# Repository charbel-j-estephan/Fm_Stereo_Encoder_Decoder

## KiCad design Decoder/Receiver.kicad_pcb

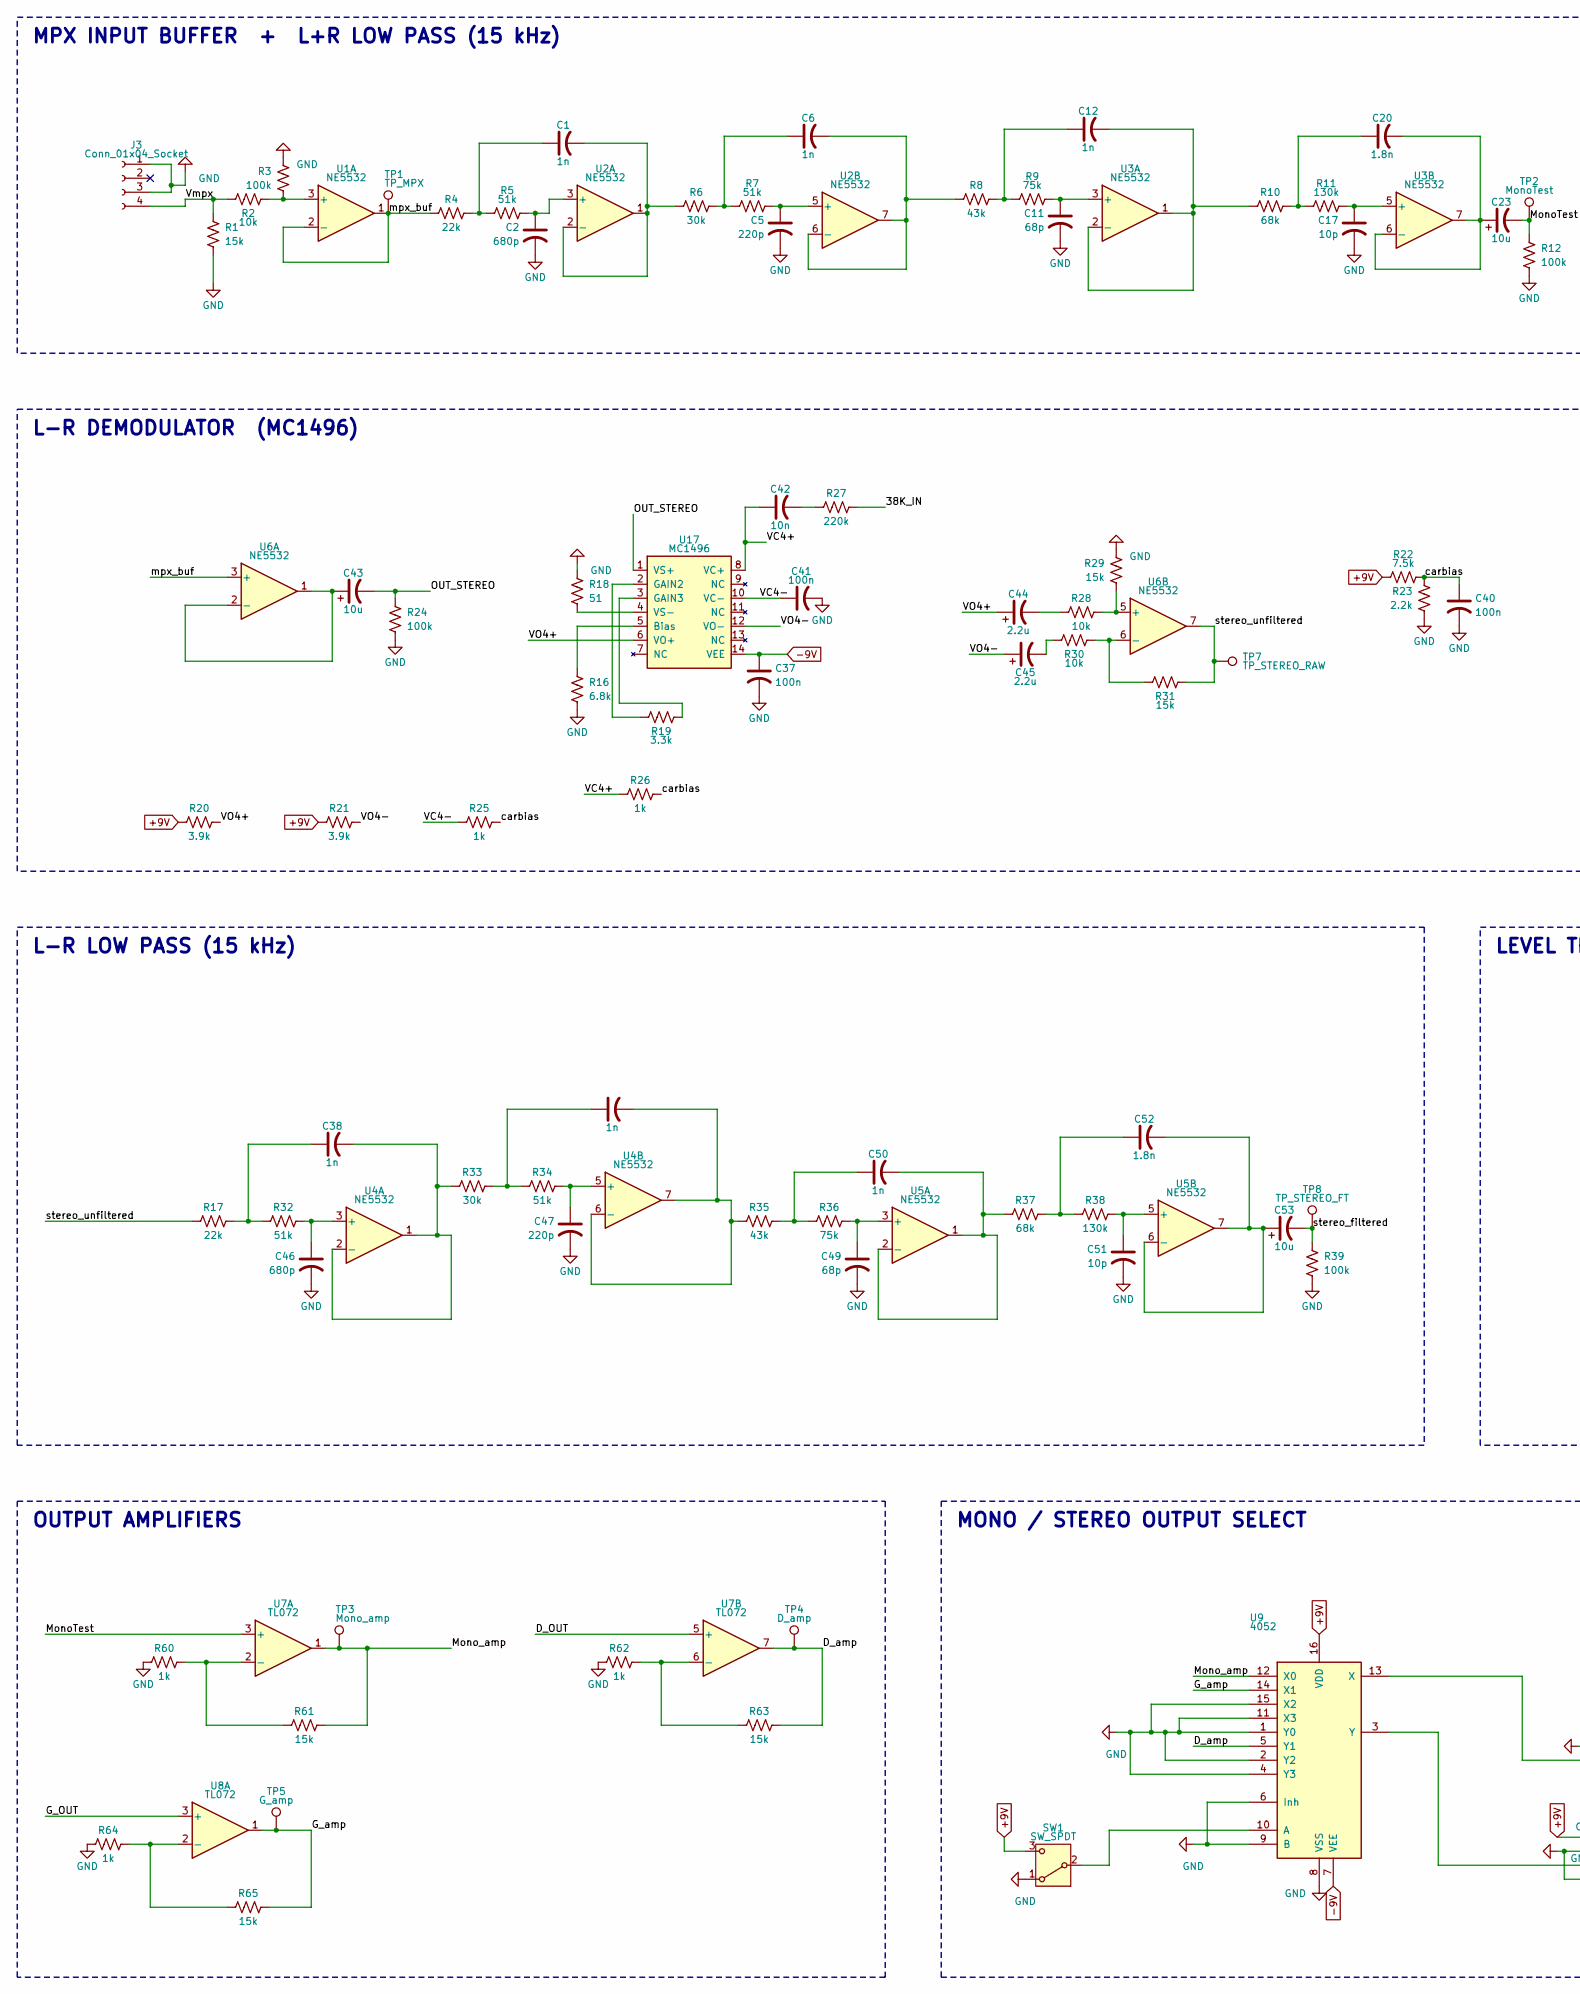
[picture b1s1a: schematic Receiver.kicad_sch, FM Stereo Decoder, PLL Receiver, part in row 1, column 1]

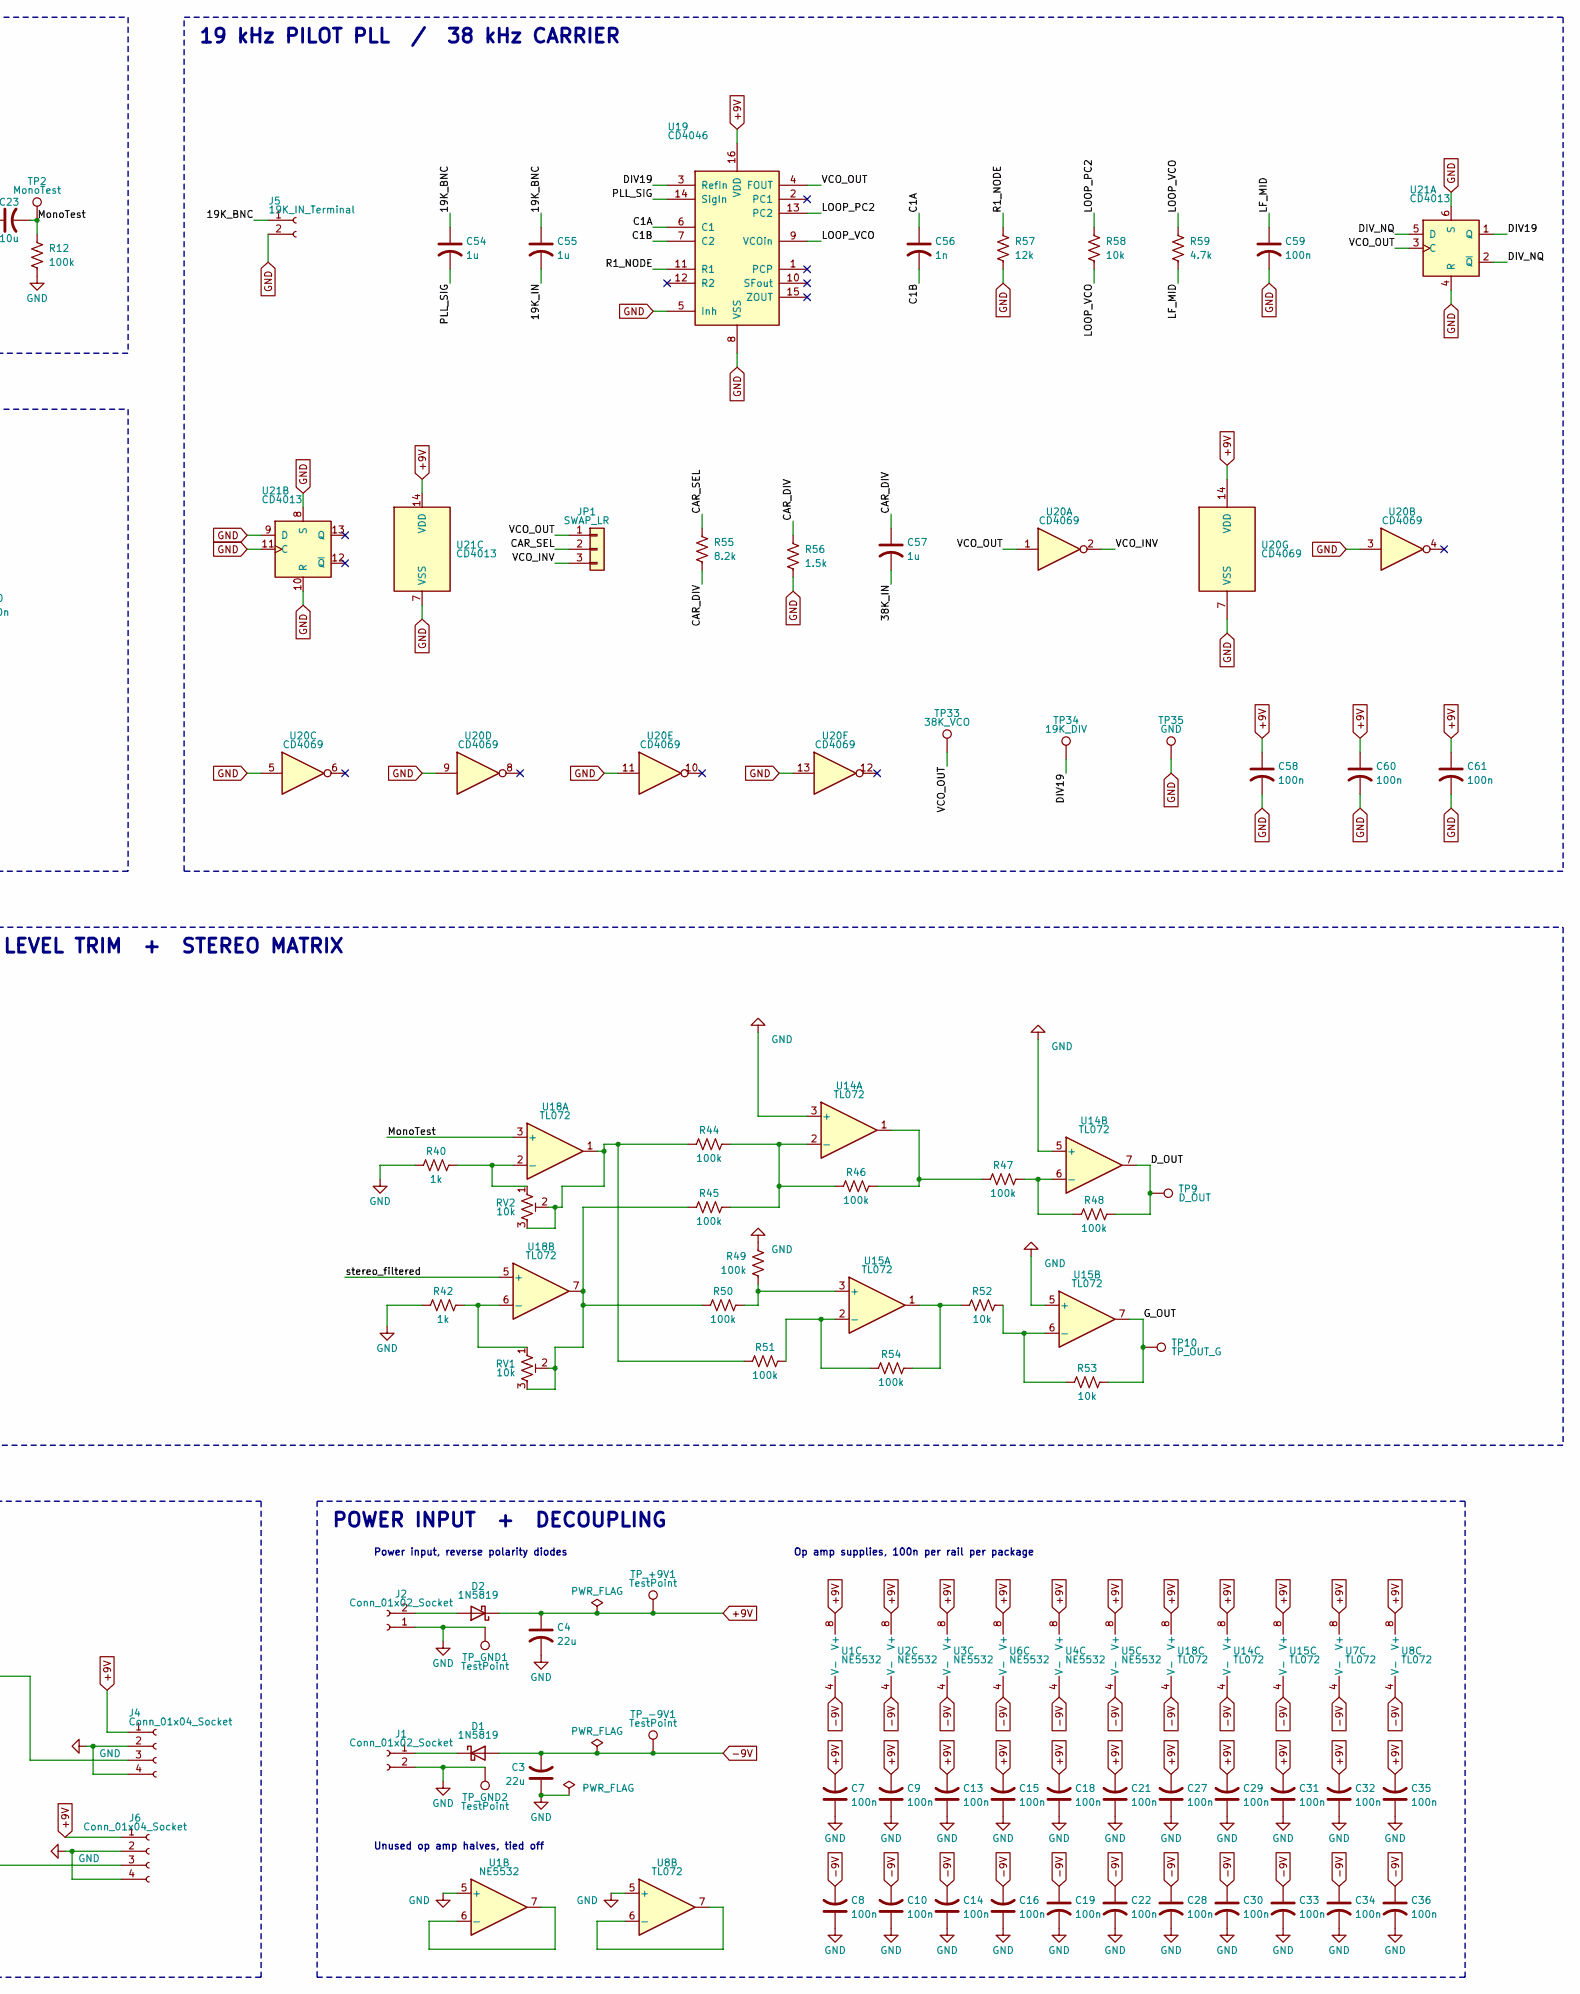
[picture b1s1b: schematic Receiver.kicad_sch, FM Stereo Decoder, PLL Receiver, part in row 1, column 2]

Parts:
C1, C6, C12, C38, C48, C50, C56: 1n; C_Disc_D5.0mm_W2.5mm_P5.00mm
C2, C46: 680p; C_Disc_D5.0mm_W2.5mm_P5.00mm
C3, C4: 22u; CP_Radial_D8.0mm_P3.50mm
C5, C47: 220p; C_Disc_D5.0mm_W2.5mm_P5.00mm
C7, C8, C9, C10, C13, C14, C15, C16, C18, C19, C21, C22, C27, C28, C29, C30, C31, C32, C33, C34, C35, C36, C37, C40, C41, C58, C59, C60, C61: 100n; C_Disc_D5.0mm_W2.5mm_P5.00mm
C11, C49: 68p; C_Disc_D5.0mm_W2.5mm_P5.00mm
C17, C51: 10p; C_Disc_D5.0mm_W2.5mm_P5.00mm
C20, C52: 1.8n; C_Disc_D5.0mm_W2.5mm_P5.00mm
C23, C43, C53: 10u; CP_Radial_D6.3mm_P2.50mm
C42: 10n; C_Disc_D5.0mm_W2.5mm_P5.00mm
C44, C45: 2.2u; CP_Radial_D6.3mm_P2.50mm
C54, C55, C57: 1u; C_Rect_L7.2mm_W3.5mm_P5.00mm
D1, D2: 1N5819; D_DO-41_SOD81_P10.16mm_Horizontal
J1, J2: Conn_01x02_Socket; TerminalBlock_Phoenix_MKDS-1,5-2-5.08_1x02_P5.08mm_Horizont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
J3: Conn_01x04_Socket; PinHeader_1x04_P2.54mm_Vertical
J4, J6: Conn_01x04_Socket; PinSocket_1x04_P2.54mm_Vertical
J5: 19K_IN_Terminal; TerminalBlock_Phoenix_MKDS-1,5-2-5.08_1x02_P5.08mm_Horizont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
JP1: SWAP_LR; PinHeader_1x03_P2.54mm_Vertical
R1, R29, R31, R61, R63, R65: 15k; R_Axial_DIN0207_L6.3mm_D2.5mm_P10.16mm_Horizontal
R2, R28, R30, R52, R53, R58: 10k; R_Axial_DIN0207_L6.3mm_D2.5mm_P10.16mm_Horizontal
R3, R12, R24, R39, R44, R45, R46, R47, R48, R49, R50, R51, R54: 100k; R_Axial_DIN0207_L6.3mm_D2.5mm_P10.16mm_Horizontal
R4, R17: 22k; R_Axial_DIN0207_L6.3mm_D2.5mm_P10.16mm_Horizontal
R5, R7, R32, R34: 51k; R_Axial_DIN0207_L6.3mm_D2.5mm_P10.16mm_Horizontal
R6, R33: 30k; R_Axial_DIN0207_L6.3mm_D2.5mm_P10.16mm_Horizontal
R8, R35: 43k; R_Axial_DIN0207_L6.3mm_D2.5mm_P10.16mm_Horizontal
R9, R36: 75k; R_Axial_DIN0207_L6.3mm_D2.5mm_P10.16mm_Horizontal
R10, R37: 68k; R_Axial_DIN0207_L6.3mm_D2.5mm_P10.16mm_Horizontal
R11, R38: 130k; R_Axial_DIN0207_L6.3mm_D2.5mm_P10.16mm_Horizontal
R16: 6.8k; R_Axial_DIN0207_L6.3mm_D2.5mm_P10.16mm_Horizontal
R18: 51; R_Axial_DIN0207_L6.3mm_D2.5mm_P10.16mm_Horizontal
R19: 3.3k; R_Axial_DIN0207_L6.3mm_D2.5mm_P10.16mm_Horizontal
R20, R21: 3.9k; R_Axial_DIN0207_L6.3mm_D2.5mm_P10.16mm_Horizontal
R22: 7.5k; R_Axial_DIN0207_L6.3mm_D2.5mm_P10.16mm_Horizontal
R23: 2.2k; R_Axial_DIN0207_L6.3mm_D2.5mm_P10.16mm_Horizontal
R25, R26, R40, R42, R60, R62, R64: 1k; R_Axial_DIN0207_L6.3mm_D2.5mm_P10.16mm_Horizontal
R27: 220k; R_Axial_DIN0207_L6.3mm_D2.5mm_P10.16mm_Horizontal
R55: 8.2k; R_Axial_DIN0207_L6.3mm_D2.5mm_P10.16mm_Horizontal
R56: 1.5k; R_Axial_DIN0207_L6.3mm_D2.5mm_P10.16mm_Horizontal
R57: 12k; R_Axial_DIN0207_L6.3mm_D2.5mm_P10.16mm_Horizontal
R59: 4.7k; R_Axial_DIN0207_L6.3mm_D2.5mm_P10.16mm_Horizontal
RV1, RV2: 10k; Potentiometer_Bourns_3296W_Vertical
SW1: SW_SPDT; PinHeader_1x03_P2.54mm_Vertical
TP1: TP_MPX; PinHeader_1x01_P2.54mm_Vertical
TP2: MonoTest; PinHeader_1x01_P2.54mm_Vertical
TP3: Mono_amp; PinHeader_1x01_P2.54mm_Vertical
TP4: D_amp; PinHeader_1x01_P2.54mm_Vertical
TP5: G_amp; PinHeader_1x01_P2.54mm_Vertical
TP7: TP_STEREO_RAW; PinHeader_1x01_P2.54mm_Vertical
TP8: TP_STEREO_FT; PinHeader_1x01_P2.54mm_Vertical
TP9: D_OUT; PinHeader_1x01_P2.54mm_Vertical
TP10: TP_OUT_G; PinHeader_1x01_P2.54mm_Vertical
TP33: 38K_VCO; PinHeader_1x01_P2.54mm_Vertical
TP34: 19K_DIV; PinHeader_1x01_P2.54mm_Vertical
TP35: GND; PinHeader_1x01_P2.54mm_Vertical
TP_+9V1: TestPoint; PinHeader_1x01_P2.54mm_Vertical
TP_-9V1: TestPoint; PinHeader_1x01_P2.54mm_Vertical
TP_GND1, TP_GND2: TestPoint; PinHeader_1x01_P2.54mm_Vertical
U1, U2, U3, U4, U5, U6: NE5532; DIP-8_W7.62mm_Socket
U7, U8, U14, U15, U18: TL072; DIP-8_W7.62mm_Socket
U9: 4052; DIP-16_W7.62mm_Socket
U17: MC1496; DIP-14_W7.62mm_Socket
U19: CD4046; DIP-16_W7.62mm_Socket
U20: CD4069; DIP-14_W7.62mm_Socket
U21: CD4013; DIP-14_W7.62mm_Socket

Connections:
+9V: C4.1, C7.2, C9.2, C13.2, C15.2, C18.2, C21.2, C27.2, C29.2, C31.2, C32.2, C35.2, C58.1, C60.1, C61.1, D2.1 (K), J4.1, J6.1, R20.2, R21.2, R22.2, SW1.3 (C), TP_+9V1.1 (1_1), U1.8 (V+), U2.8 (V+), U3.8 (V+), U4.8 (V+), U5.8 (V+), U6.8 (V+), U7.8 (V+), U8.8 (V+), U9.16 (VDD), U14.8 (V+), U15.8 (V+), U18.8 (V+), U19.16 (VDD), U20.14 (VDD), U21.14 (VDD)
-9V: C3.2, C8.2, C10.2, C14.2, C16.2, C19.1, C22.1, C28.1, C30.1, C33.1, C34.1, C36.1, C37.1, D1.2 (A), TP_-9V1.1 (1_1), U1.4 (V-), U2.4 (V-), U3.4 (V-), U4.4 (V-), U5.4 (V-), U6.4 (V-), U7.4 (V-), U8.4 (V-), U9.7 (VEE), U14.4 (V-), U15.4 (V-), U17.14 (VEE), U18.4 (V-)
/19K_BNC: C54.1, C55.1, J5.1
/19K_IN: C55.2
/38K_IN: C57.2, R27.1
/C1A: C56.1, U19.6 (C1)
/C1B: C56.2, U19.7 (C2)
/CAR_DIV: C57.1, R55.2, R56.1
/CAR_SEL: JP1.2, R55.1
/DIV19: TP34.1 (1_1), U19.3 (RefIn), U21.1 (Q)
/DIV_NQ: U21.2 (~Q), U21.5 (D)
/D_OUT: R48.1, TP9.1 (1_1), U7.5 (+), U14.7
/D_amp: R63.1, TP4.1 (1_1), U7.7, U9.5 (Y1)
/G_OUT: R53.1, TP10.1 (1_1), U8.3 (+), U15.7
/G_amp: R65.1, TP5.1 (1_1), U8.1, U9.14 (X1)
/LF_MID: C59.1, R59.2
/LOOP_PC2: R58.1, U19.13 (PC2)
/LOOP_VCO: R58.2, R59.1, U19.9 (VCOin)
/MonoTest: C23.2, R12.2, TP2.1 (1_1), U7.3 (+), U18.3 (+)
/Mono_amp: R61.1, TP3.1 (1_1), U7.1, U9.12 (X0)
/OUT_STEREO: C43.2, R24.2, U17.1 (VS+)
/PLL_SIG: C54.2, U19.14 (SigIn)
/R1_NODE: R57.1, U19.11 (R1)
/VC4+: C42.1, R26.2, U17.8 (VC+)
/VC4-: C41.1, R25.2, U17.10 (VC-)
/VCO_INV: JP1.3, U20.2
/VCO_OUT: JP1.1, TP33.1 (1_1), U19.4 (FOUT), U20.1, U21.3 (C)
/VO4+: C44.1, R20.1, U17.6 (VO+)
/VO4-: C45.1, R21.1, U17.12 (VO-)
/Vmpx: J3.4, R1.1, R2.1
/carbias: C40.1, R22.1, R23.1, R25.1, R26.1
/mpx_buf: R4.1, TP1.1 (1_1), U1.1, U1.2 (-), U6.3 (+)
/stereo_filtered: C53.2, R39.2, TP8.1 (1_1), U18.5 (+)
/stereo_unfiltered: R17.1, R31.1, TP7.1 (1_1), U6.7
GND: C2.2, C3.1, C4.2, C5.2, C7.1, C8.1, C9.1, C10.1, C11.2, C13.1, C14.1, C15.1, C16.1, C17.2, C18.1, C19.2, C21.1, C22.2, C27.1, C28.2, C29.1, C30.2, C31.1, C32.1, C33.2, C34.2, C35.1, C36.2, C37.2, C40.2, C41.2, C46.2, C47.2, C49.2, C51.2, C58.2, C59.2, C60.2, C61.2, J1.2, J2.1, J3.1, J3.3, J4.2, J4.4, J5.2, J6.2, J6.4, R1.2, R3.1, R12.1, R16.1, R18.1, R23.2, R24.1, R29.1, R39.1, R40.2, R42.2, R49.1, R56.2, R57.2, R60.2, R62.2, R64.2, SW1.1 (A), TP35.1 (1_1), TP_GND1.1 (1_1), TP_GND2.1 (1_1), U1.5 (+), U8.5 (+), U9.1 (Y0), U9.2 (Y2), U9.4 (Y3), U9.6 (Inh), U9.8 (VSS), U9.9 (B), U9.11 (X3), U9.15 (X2), U14.3 (+), U14.5 (+), U15.5 (+), U19.5 (Inh), U19.8 (VSS), U20.3, U20.5, U20.7 (VSS), U20.9, U20.11, U20.13, U21.4 (R), U21.6 (S), U21.7 (VSS), U21.8 (S), U21.9 (D), U21.10 (R), U21.11 (C)
unnamed: C1.1, R4.2, R5.1
unnamed: C6.1, R6.2, R7.1
unnamed: C12.1, R8.2, R9.1
unnamed: C20.1, R10.2, R11.1
unnamed: C38.1, R17.2, R32.1
unnamed: C42.2, R27.2
unnamed: C44.2, R28.2
unnamed: C45.2, R30.2
unnamed: C48.1, R33.2, R34.1
unnamed: C50.1, R35.2, R36.1
unnamed: C52.1, R37.2, R38.1
unnamed: D1.1 (K), J1.1
unnamed: D2.2 (A), J2.2
unnamed: J4.3, U9.13 (X)
unnamed: J6.3, U9.3 (Y)
unnamed: R44.2, R51.2, RV2.2, RV2.3, U18.1
unnamed: R45.2, R50.2, RV1.2, RV1.3, U18.7
unnamed: R46.1, R47.2, U14.1
unnamed: R52.2, R54.1, U15.1
unnamed: SW1.2 (B), U9.10 (A)
unnamed: R2.2, R3.2, U1.3 (+)
unnamed: U1.6 (-), U1.7
unnamed: C2.1, R5.2, U2.3 (+)
unnamed: C1.2, R6.1, U2.1, U2.2 (-)
unnamed: C5.1, R7.2, U2.5 (+)
unnamed: C6.2, R8.1, U2.6 (-), U2.7
unnamed: C11.1, R9.2, U3.3 (+)
unnamed: C12.2, R10.1, U3.1, U3.2 (-)
unnamed: C17.1, R11.2, U3.5 (+)
unnamed: C20.2, C23.1, U3.6 (-), U3.7
unnamed: C46.1, R32.2, U4.3 (+)
unnamed: C38.2, R33.1, U4.1, U4.2 (-)
unnamed: C47.1, R34.2, U4.5 (+)
unnamed: C48.2, R35.1, U4.6 (-), U4.7
unnamed: C49.1, R36.2, U5.3 (+)
unnamed: C50.2, R37.1, U5.1, U5.2 (-)
unnamed: C51.1, R38.2, U5.5 (+)
unnamed: C52.2, C53.1, U5.6 (-), U5.7
unnamed: C43.1, U6.1, U6.2 (-)
unnamed: R28.1, R29.2, U6.5 (+)
unnamed: R30.1, R31.2, U6.6 (-)
unnamed: R60.1, R61.2, U7.2 (-)
unnamed: R62.1, R63.2, U7.6 (-)
unnamed: R64.1, R65.2, U8.2 (-)
unnamed: U8.6 (-), U8.7
unnamed: R44.1, R45.1, R46.2, U14.2 (-)
unnamed: R47.1, R48.2, U14.6 (-)
unnamed: R49.2, R50.1, U15.3 (+)
unnamed: R51.1, R54.2, U15.2 (-)
unnamed: R52.1, R53.2, U15.6 (-)
unnamed: R16.2, U17.5 (Bias)
unnamed: R19.2, U17.2 (GAIN2)
unnamed: R19.1, U17.3 (GAIN3)
unnamed: R18.2, U17.4 (VS-)
unnamed: R40.1, RV2.1, U18.2 (-)
unnamed: R42.1, RV1.1, U18.6 (-)

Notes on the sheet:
MPX INPUT BUFFER + L+R LOW PASS (15 kHz)
L-R DEMODULATOR (MC1496)
19 kHz PILOT PLL / 38 kHz CARRIER
L-R LOW PASS (15 kHz)
LEVEL TRIM + STEREO MATRIX
OUTPUT AMPLIFIERS
MONO / STEREO OUTPUT SELECT
POWER INPUT + DECOUPLING
Power input, reverse polarity diodes
Op amp supplies, 100n per rail per package
Unused op amp halves, tied off

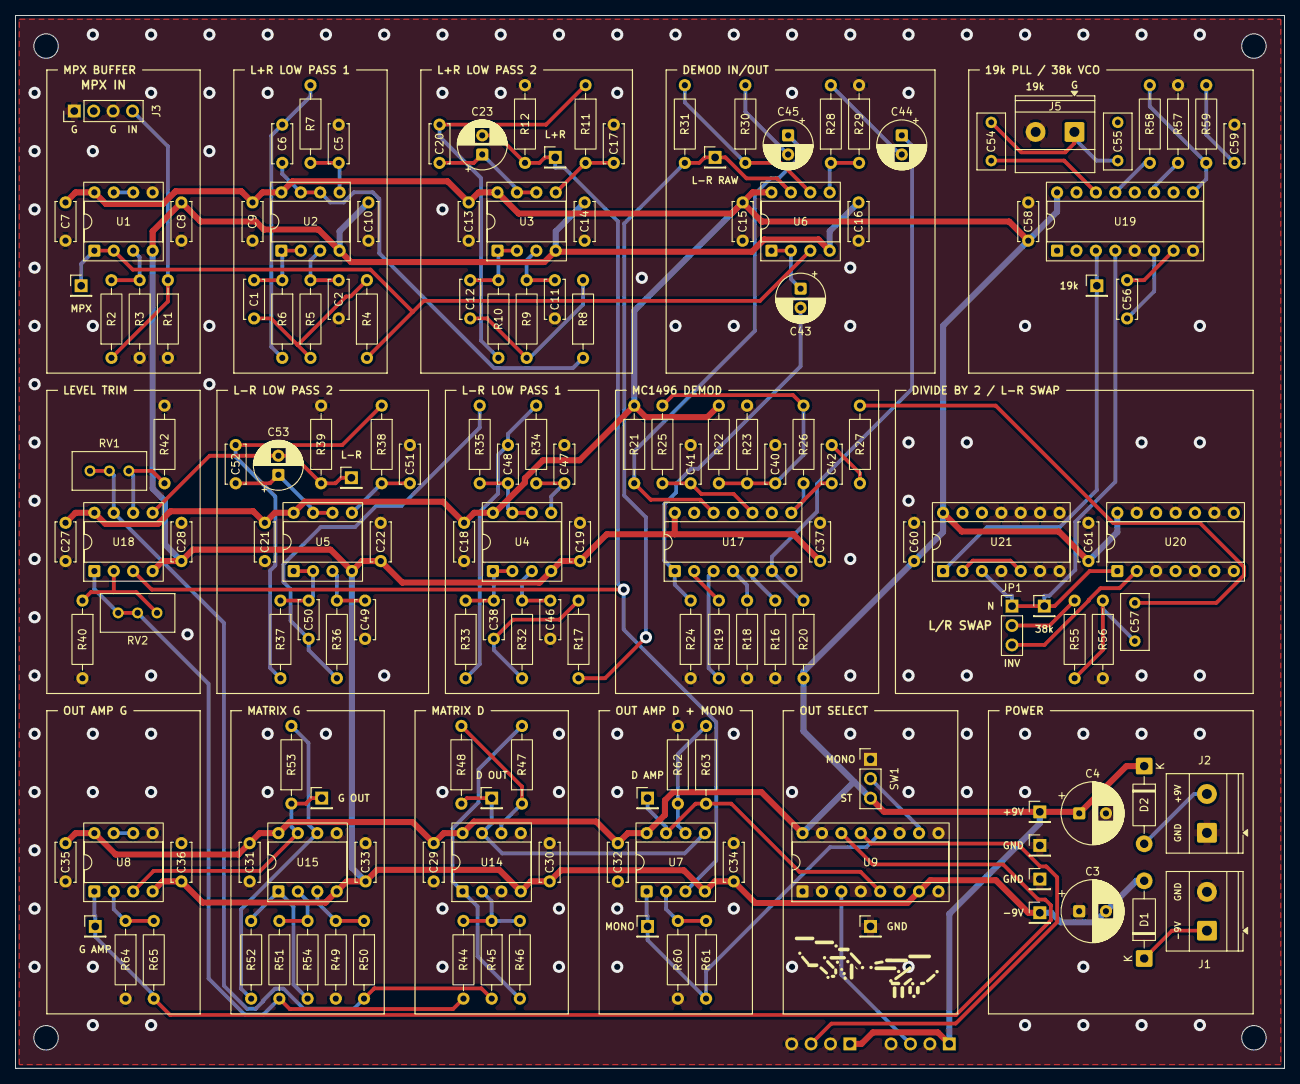
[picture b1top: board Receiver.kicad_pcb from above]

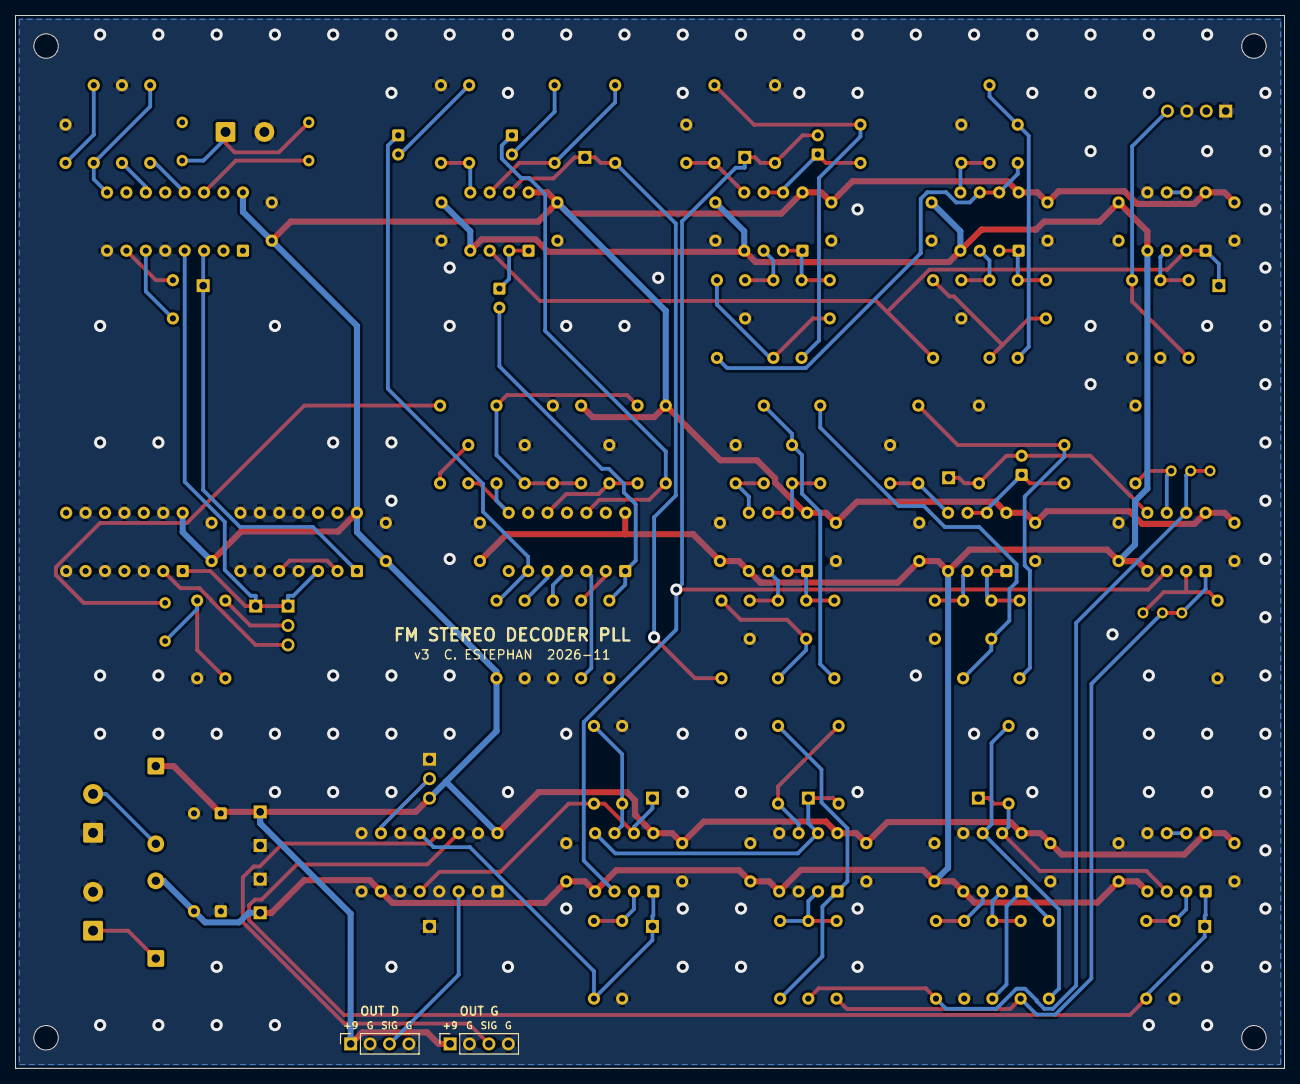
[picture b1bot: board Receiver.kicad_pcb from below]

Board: 2 copper layers, 166.0 x 137.7 mm, 161 parts (2 on the bottom side), 90 nets.
